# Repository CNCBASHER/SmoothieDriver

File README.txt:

SmoothieDriverDualDC is an open source two channel closed loop feedback dc motor controller using an arm cortex-m0 mcu (lpc1227) to drive two +-1.5A full h-bridge drivers (a4973).

The firmware is compiled using the LPCXpresso Studio for now.

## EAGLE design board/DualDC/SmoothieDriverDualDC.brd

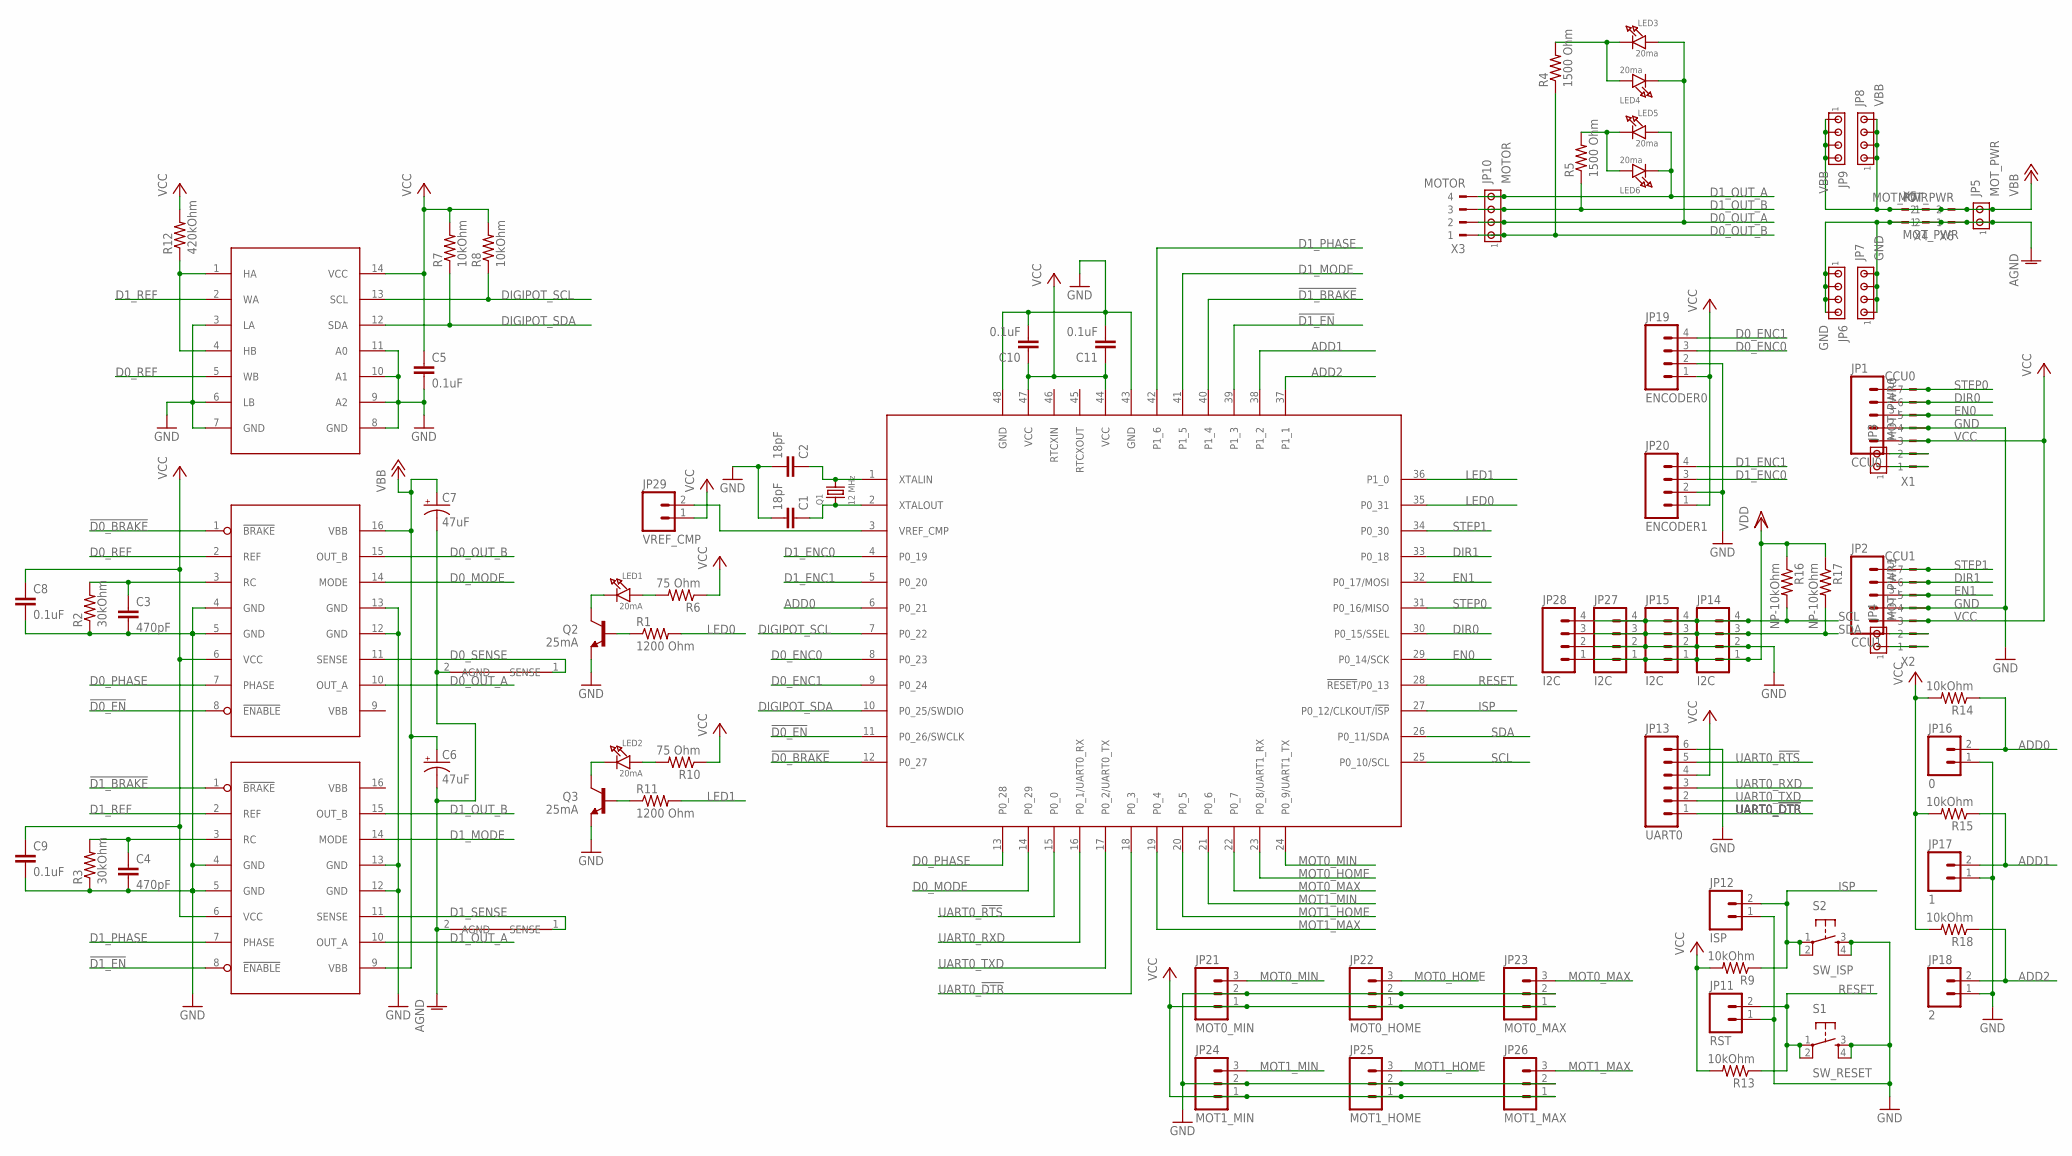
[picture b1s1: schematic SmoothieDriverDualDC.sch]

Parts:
C1, C2: 18pF; C0603
C3, C4: 470pF; C0603
C5, C8, C9, C10, C11: 0.1uF; C0603
C6, C7: 47uF; PANASONIC_D
JP1: CCU0; 1X05
JP2: CCU1; 1X05
JP3: MOT_PWR0; 10X02MTA
JP4: MOT_PWR1; 10X02MTA
JP5: MOT_PWR; 10X02MTA
JP6, JP7: GND; 10X04MTA
JP8, JP9: VBB; 10X04MTA
JP10: MOTOR; 10X04MTA
JP11: RST; 1X02
JP12: ISP; 1X02
JP13: UART0; 1X06
JP14, JP15, JP27, JP28: I2C; 1X04
JP16: 0; 1X02
JP17: 1; 1X02
JP18: 2; 1X02
JP19: ENCODER0; 1X04
JP20: ENCODER1; 1X04
JP21: MOT0_MIN; 1X03
JP22: MOT0_HOME; 1X03
JP23: MOT0_MAX; 1X03
JP24: MOT1_MIN; 1X03
JP25: MOT1_HOME; 1X03
JP26: MOT1_MAX; 1X03
JP29: VREF_CMP; 1X02
LED1, LED2: 20mA; CHIPLED_0805
LED3, LED4, LED5, LED6: 20ma; CHIPLED_0805
MCU1: LPC1227; LQFP48
Q1: 12 MHz; CRYSTAL_3.2X2.5
Q2, Q3: 25mA; SOT23
R1, R11: 1200 Ohm; R0603
R2, R3: 30kOhm; R0603
R4, R5: 1500 Ohm; R0603
R6, R10: 75 Ohm; R0603
R7, R8, R9, R13, R14, R15, R18: 10kOhm; R0603
R12: 420kOhm; R0603
R16, R17: NP-10kOhm; R0603
S1: SW_RESET; TACTILE_SWITCH_SMD
S2: SW_ISP; TACTILE_SWITCH_SMD
U1: MAX5387-50kOhm; TSSOP14
U2, U3: A4973; SO16L
U$1, U$2: CONNECTOR; CONNECT
X1: CCU0; 180G-7
X2: CCU1; 180G-7
X3: MOTOR; 180G-4
X4, X5, X6: MOT_PWR; 180G-2

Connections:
!D0_BRAKE: MCU1.12 (P0_27), U2.1 (!BRAKE)
!D0_EN: MCU1.11 (P0_26/SWCLK), U2.8 (!ENABLE)
!D1_BRAKE: MCU1.40 (P1_4), U3.1 (!BRAKE)
!D1_EN: MCU1.39 (P1_3), U3.8 (!ENABLE)
ADD0: JP16.2, MCU1.6 (P0_21), R14.1
ADD1: JP17.2, MCU1.38 (P1_2), R15.1
ADD2: JP18.2, MCU1.37 (P1_1), R18.1
AGND: C6.-, C7.-, JP5.1, JP6.1, JP6.2, JP6.3, JP6.4, JP7.1, JP7.2, JP7.3, JP7.4, U$1.2 (AGND), U$2.2 (AGND), X4.1, X5.2, X6.1
D0_ENC0: JP19.3, MCU1.8 (P0_23)
D0_ENC1: JP19.4, MCU1.9 (P0_24)
D0_MODE: MCU1.14 (P0_29), U2.14 (MODE)
D0_OUT_A: JP10.2, LED3.A, LED4.C, U2.10 (OUT_A), X3.2
D0_OUT_B: JP10.1, R4.1, U2.15 (OUT_B), X3.1
D0_PHASE: MCU1.13 (P0_28), U2.7 (PHASE)
D0_REF: U1.5 (WB), U2.2 (REF)
D0_SENSE: U2.11 (SENSE), U$2.1 (SENSE)
D1_ENC0: JP20.3, MCU1.4 (P0_19)
D1_ENC1: JP20.4, MCU1.5 (P0_20)
D1_MODE: MCU1.41 (P1_5), U3.14 (MODE)
D1_OUT_A: JP10.4, LED5.A, LED6.C, U3.10 (OUT_A), X3.4
D1_OUT_B: JP10.3, R5.1, U3.15 (OUT_B), X3.3
D1_PHASE: MCU1.42 (P1_6), U3.7 (PHASE)
D1_REF: U1.2 (WA), U3.2 (REF)
D1_SENSE: U3.11 (SENSE), U$1.1 (SENSE)
DIGIPOT_SCL: MCU1.7 (P0_22), R8.1, U1.13 (SCL)
DIGIPOT_SDA: MCU1.10 (P0_25/SWDIO), R7.1, U1.12 (SDA)
DIR0: JP1.4, MCU1.30 (P0_15/SSEL), X1.6
DIR1: JP2.4, MCU1.33 (P0_18), X2.6
EN0: JP1.3, MCU1.29 (P0_14/SCK), X1.5
EN1: JP2.3, MCU1.32 (P0_17/MOSI), X2.5
GND: C1.2, C2.2, C3.2, C4.2, C5.2, C8.2, C9.2, C10.2, C11.2, JP1.2, JP2.2, JP11.1, JP12.1, JP13.6, JP14.2, JP15.2, JP16.1, JP17.1, JP18.1, JP19.2, JP20.2, JP21.2, JP22.2, JP23.2, JP24.2, JP25.2, JP26.2, JP27.2, JP28.2, MCU1.43 (GND), MCU1.48 (GND), Q2.2 (E), Q3.2 (E), R2.1, R3.1, S1.3, S1.4, S2.3, S2.4, U1.3 (LA), U1.6 (LB), U1.7 (GND), U1.8 (GND), U1.9 (A2), U1.10 (A1), U1.11 (A0), U2.4 (GND), U2.5 (GND), U2.12 (GND), U2.13 (GND), U3.4 (GND), U3.5 (GND), U3.12 (GND), U3.13 (GND), X1.4, X2.4
ISP: JP12.2, MCU1.27 (P0_12/CLKOUT/!ISP), R9.1, S2.1, S2.2
LED0: MCU1.35 (P0_31), R1.2
LED1: MCU1.36 (P1_0), R11.2
MOT0_HOME: JP22.3, MCU1.23 (P0_8/UART1_RX)
MOT0_MAX: JP23.3, MCU1.22 (P0_7)
MOT0_MIN: JP21.3, MCU1.24 (P0_9/UART1_TX)
MOT1_HOME: JP25.3, MCU1.20 (P0_5)
MOT1_MAX: JP26.3, MCU1.19 (P0_4)
MOT1_MIN: JP24.3, MCU1.21 (P0_6)
unnamed: LED1.A, R6.2
unnamed: LED1.C, Q2.3 (C)
unnamed: C3.1, R2.2, U2.3 (RC)
unnamed: C2.1, MCU1.1 (XTALIN), Q1.2
unnamed: C1.1, MCU1.2 (XTALOUT), Q1.1
unnamed: Q2.1 (B), R1.1
unnamed: Q3.1 (B), R11.1
unnamed: C4.1, R3.2, U3.3 (RC)
unnamed: LED2.A, R10.2
unnamed: LED2.C, Q3.3 (C)
unnamed: R12.1, U1.1 (HA), U1.4 (HB)
unnamed: LED5.C, LED6.A, R5.2
unnamed: LED3.C, LED4.A, R4.2
unnamed: JP4.2, X2.2
unnamed: JP4.1, X2.1
unnamed: JP3.2, X1.2
unnamed: JP3.1, X1.1
unnamed: JP29.2, MCU1.3 (VREF_CMP)
RESET: JP11.2, MCU1.28 (!RESET!/P0_13), R13.1, S1.1, S1.2
SCL: JP14.4, JP15.4, JP27.4, JP28.4, MCU1.25 (P0_10/SCL), R16.2
SDA: JP14.3, JP15.3, JP27.3, JP28.3, MCU1.26 (P0_11/SDA), R17.2
STEP0: JP1.5, MCU1.31 (P0_16/MISO), X1.7
STEP1: JP2.5, MCU1.34 (P0_30), X2.7
UART0_!DTR!: JP13.1, MCU1.18 (P0_3)
UART0_!RTS!: JP13.5, MCU1.15 (P0_0)
UART0_RXD: JP13.3, MCU1.16 (P0_1/UART0_RX)
UART0_TXD: JP13.2, MCU1.17 (P0_2/UART0_TX)
VBB: C6.+, C7.+, JP5.2, JP8.1, JP8.2, JP8.3, JP8.4, JP9.1, JP9.2, JP9.3, JP9.4, U2.16 (VBB), U3.9 (VBB), X4.2, X5.1, X6.2
VCC: C5.1, C8.1, C9.1, C10.1, C11.1, JP1.1, JP2.1, JP13.4, JP19.1, JP20.1, JP21.1, JP22.1, JP23.1, JP24.1, JP25.1, JP26.1, JP29.1, MCU1.44 (VCC), MCU1.47 (VCC), R6.1, R7.2, R8.2, R9.2, R10.1, R12.2, R13.2, R14.2, R15.2, R18.2, U1.14 (VCC), U2.6 (VCC), U3.6 (VCC), X1.3, X2.3
VDD: JP14.1, JP15.1, JP27.1, JP28.1, R16.1, R17.1

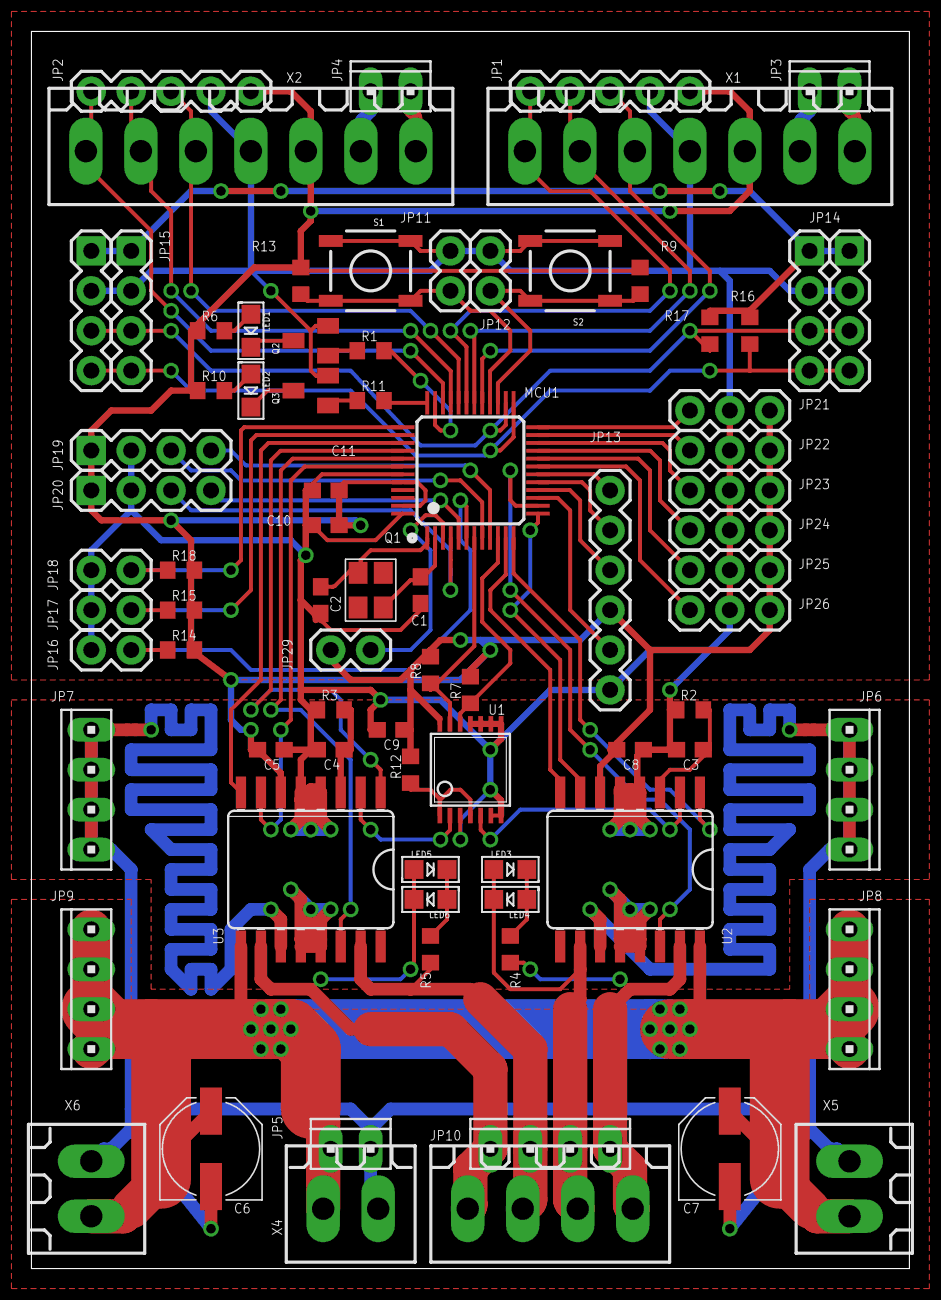
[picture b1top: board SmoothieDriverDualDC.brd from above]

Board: 2 copper layers, 55.9 x 78.7 mm, 81 parts (0 on the bottom side), 70 nets.

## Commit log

2012-08-14 Initial commit of proto board and proto firmware

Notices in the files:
parts and their libraries:
SparkFun: Licensing: CC v3.0 Share-Alike You are welcome to use this library for commercial purposes.
